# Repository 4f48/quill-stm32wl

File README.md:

# Quill STM32 WL

An Adafruit Feather-sized STM32 development board with integrated 868 MHz LoRa radio.

## Features
- 32-bit ARM Cortex-M4 48 MHz microcontroller
- 256 kb flash, 64 kb RAM
- LoRa P2P/LoRaWAN - Up to 15 km range with a good antenna
- Programmable via SWD/UART/USB or control with AT Commands
- Built-in 3.3V linear regulator, providing up to 600 mA
- JST PH battery connector, built-in charging
- USB-C port for power supply, USB serial, battery charging
- Adafruit Feather-compatible dimensions
- STEMMA QT/Qwiic connector for soldering-free I2C

## Why though
I made Quill STM32 WL because I was unsatisfied with existing LoRa/long-range wireless development boards. They are either low-effort modules with ESP32 chips and huge power consumption, or use outdated parts and standards. I really liked the Adafruit Feather RP2040 RFM95 due to its size, feature-set, but it uses the older Semtech SX1276 LoRa IC.

As I was scrolling through ST Microelectronic's website (as one does), I found the perfect match: the STM32WLE5 family of microcontrollers. They offer an improved LoRa solution - with up to +22 dBm output power - in a sleek package, with an integrated, low-power STM32 microcontroller. I knew I had to try making something with it.

This was my second PCB project ever, and digging into more complicated concepts and trying to make a more dense board layout was a great challenge and an opportunity to improve my skills, before starting even more complicated projects.

## Usage
You can either use Quill STM32 WL as a standalone microcontroller, by programming it via the 3-pin SWD port or USB serial, or by sending AT Commands to the UART2 serial bus on pins 12 (RX) and 13 (TX) if you just wish to use the LoRa/LoRaWAN capabilities.

For programming instructions, see [RAK3172 Low Level Development Reference](https://docs.rakwireless.com/product-categories/wisduo/rak3172-module/low-level-development/). For using the AT Command interface, see [RAK3172 AT Command Manual](https://docs.rakwireless.com/product-categories/wisduo/rak3172-module/at-command-manual/).

This board is really versatile and could be used for a wide variety of projects. Note that the MCU is not as fast as some other offerings on the market, thus it can't be used for advanced data processing. However, Quill STM32 WL is more than capable of driving sensors (for example outdoor air monitoring) and some basic processing tasks, and thanks to its LoRa capabilities, it can radio data through long distances, ideally several kilometers with clear line-of-sight, which is particularly useful for off-grid IOT systems, as an example.

## Build one yourself!
In theory, you could make one of these boards for yourself. Uploading the provided Gerber files to a PCB manufacturing service (JLCPCB, PCBWay, Aisler, etc.) is simple, not very expensive and you usually get the boards quickly. You can find the production files in [/production](https://github.com/4f48/quill-stm32wl/tree/main/production).

However, placing and soldering the SMD components on the board may prove difficult, especially if you never soldered anything before. The design uses 0402 (1005 metric) passive components to fit into the space-confined size of the board. While it may not seem like on the screen, these components are REALLY tiny. You might find it easier to have the manufacturing service mount the components for you, but that gets very expensive very fast. For example, making 5 fully assembled Quill STM32 WL with JLCPCB would cost around $130 plus shipping. Reflow/hot-air soldering is an option, but you need to have specific equipment for that.

If you still want to make one of these yourself, feel free to explore these files in this repository, they will help greatly:

- Schematic: [schematic.svg](https://github.com/4f48/quill-stm32wl/blob/main/assets/schematic.svg)
- KiCad PCB: [quill-stm32wl.kicad_pcb](https://github.com/4f48/quill-stm32wl/blob/main/quill-stm32wl.kicad_pcb)
- Bill of Materials: [bom.csv](https://github.com/4f48/quill-stm32wl/blob/main/bom.csv)/[bom.ods](https://github.com/4f48/quill-stm32wl/blob/main/bom.ods)
- 3D model: [quill_stm32wl.step](https://github.com/4f48/quill-stm32wl/blob/main/assets/quill_stm32wl.step)

## Fallout Zine
Check out the magazine page for this project. Or [download PDF](https://raw.githubusercontent.com/4f48/quill-stm32wl/refs/heads/main/assets/magazine_page.pdf).

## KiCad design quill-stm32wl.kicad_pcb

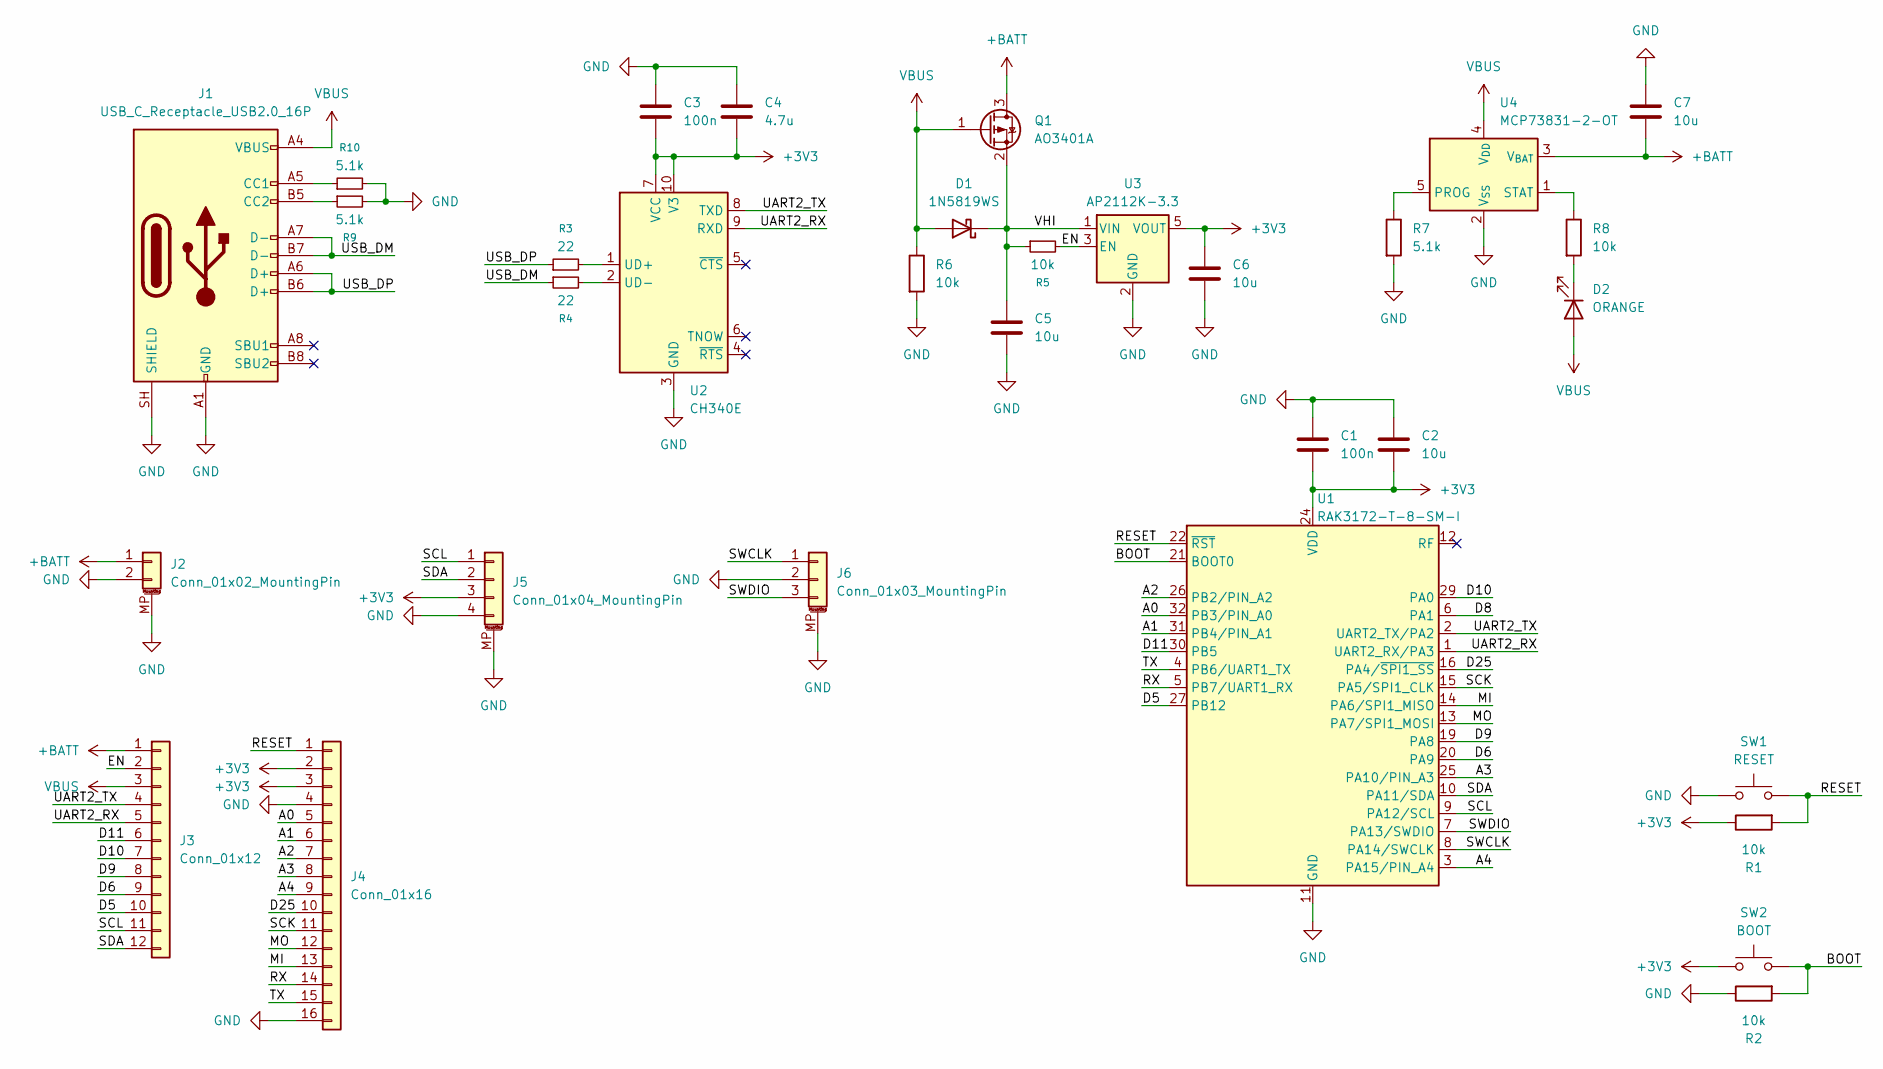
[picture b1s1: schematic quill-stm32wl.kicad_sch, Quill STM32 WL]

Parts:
C1, C3: 100n; C_0402_1005Metric
C2, C5, C6, C7: 10u; C_0603_1608Metric
C4: 4.7u; C_0402_1005Metric
D1: 1N5819WS; D_SOD-323
D2: ORANGE; LED_0402_1005Metric
J1: USB_C_Receptacle_USB2.0_16P; USB_C_Receptacle_GCT_USB4105-xx-A_16P_TopMnt_Horizontal
J2: Conn_01x02_MountingPin; JST_PH_S2B-PH-SM4-TB_1x02-1MP_P2.00mm_Horizontal
J3: Conn_01x12; PinHeader_1x12_P2.54mm_Vertical
J4: Conn_01x16; PinHeader_1x16_P2.54mm_Vertical
J5: Conn_01x04_MountingPin; JST_SH_BM04B-SRSS-TB_1x04-1MP_P1.00mm_Vertical
J6: Conn_01x03_MountingPin; JST_SH_BM03B-SRSS-TB_1x03-1MP_P1.00mm_Vertical
Q1: AO3401A; SOT-23
R1, R2, R5, R6, R8: 10k; R_0402_1005Metric
R3, R4: 22; R_0402_1005Metric
R7, R9, R10: 5.1k; R_0402_1005Metric
SW1: RESET; SW_SPST_PTS810
SW2: BOOT; SW_SPST_PTS810
U1: RAK3172-T-8-SM-I; RAK3172
U2: CH340E; MSOP-10_3x3mm_P0.5mm
U3: AP2112K-3.3; SOT-23-5
U4: MCP73831-2-OT; SOT-23-5

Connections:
+3V3: C1.2, C2.2, C3.2, C4.2, C6.1, J4.2, J4.3, J5.3, R1.1, SW2.1, U1.24 (VDD), U2.7 (VCC), U2.10 (V3), U3.5 (VOUT)
+BATT: C7.2, J2.1, J3.1, Q1.3 (D), U4.3 (V_{BAT})
/A0: J4.5, U1.32 (PB3/PIN_A0)
/A1: J4.6, U1.31 (PB4/PIN_A1)
/A2: J4.7, U1.26 (PB2/PIN_A2)
/A3: J4.8, U1.25 (PA10/PIN_A3)
/A4: J4.9, U1.3 (PA15/PIN_A4)
/BOOT: R2.2, SW2.2, U1.21 (BOOT0)
/D5: J3.10, U1.27 (PB12)
/D6: J3.9, U1.20 (PA9)
/D8: U1.6 (PA1)
/D9: J3.8, U1.19 (PA8)
/D10: J3.7, U1.29 (PA0)
/D11: J3.6, U1.30 (PB5)
/D25: J4.10, U1.16 (PA4/~SPI1_SS)
/EN: J3.2, R5.2, U3.3 (EN)
/MI: J4.13, U1.14 (PA6/SPI1_MISO)
/MO: J4.12, U1.13 (PA7/SPI1_MOSI)
/RESET: J4.1, R1.2, SW1.2, U1.22 (~RST)
/RX: J4.14, U1.5 (PB7/UART1_RX)
/SCK: J4.11, U1.15 (PA5/SPI1_CLK)
/SCL: J3.11, J5.1, U1.9 (PA12/SCL)
/SDA: J3.12, J5.2, U1.10 (PA11/SDA)
/SWCLK: J6.1, U1.8 (PA14/SWCLK)
/SWDIO: J6.3, U1.7 (PA13/SWDIO)
/TX: J4.15, U1.4 (PB6/UART1_TX)
/UART2_RX: J3.5, U1.1 (UART2_RX/PA3), U2.9 (RXD)
/UART2_TX: J3.4, U1.2 (UART2_TX/PA2), U2.8 (TXD)
/USB_DM: J1.A7 (D-), J1.B7 (D-), R4.1
/USB_DP: J1.A6 (D+), J1.B6 (D+), R3.1
/VHI: C5.1, D1.1 (K), Q1.2 (S), R5.1, U3.1 (VIN)
GND: C1.1, C2.1, C3.1, C4.1, C5.2, C6.2, C7.1, J1.A1 (GND), J1.A12 (GND), J1.B1 (GND), J1.B12 (GND), J1.SH (SHIELD), J2.2, J2.MP (MountPin), J4.4, J4.16, J5.4, J5.MP (MountPin), J6.2, J6.MP (MountPin), R2.1, R6.2, R7.2, R9.2, R10.2, SW1.1, U1.11 (GND), U1.17 (GND), U1.18 (GND), U1.23 (GND), U1.28 (GND), U2.3 (GND), U3.2 (GND), U4.2 (V_{SS})
unnamed: D2.1 (K), R8.2
unnamed: J1.A5 (CC1), R10.1
unnamed: J1.B5 (CC2), R9.1
unnamed: R3.2, U2.1 (UD+)
unnamed: R4.2, U2.2 (UD-)
unnamed: R7.1, U4.5 (PROG)
unnamed: R8.1, U4.1 (STAT)
VBUS: D1.2 (A), D2.2 (A), J1.A4 (VBUS), J1.A9 (VBUS), J1.B4 (VBUS), J1.B9 (VBUS), J3.3, Q1.1 (G), R6.1, U4.4 (V_{DD})

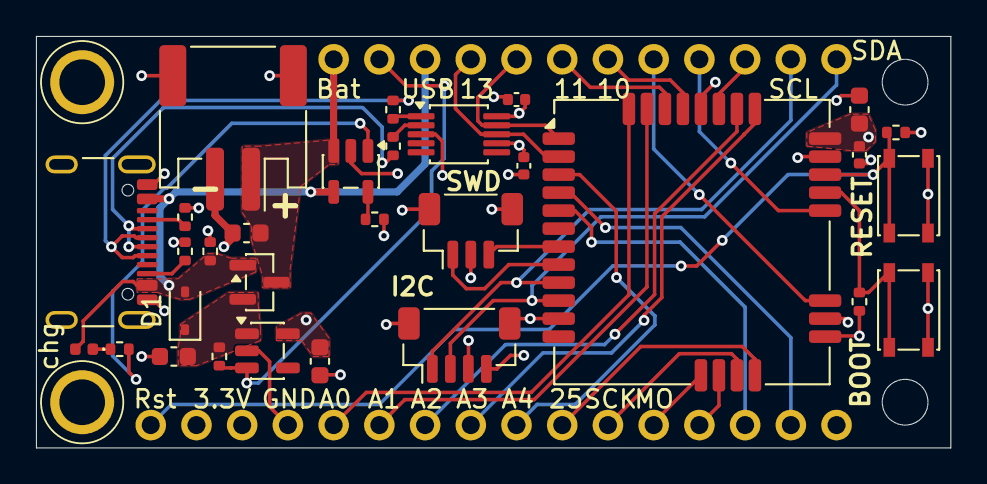
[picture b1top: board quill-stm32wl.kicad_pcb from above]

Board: 4 copper layers, 50.8 x 22.9 mm, 32 parts (0 on the bottom side), 39 nets.

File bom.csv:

Designator,Footprint,Quantity,Value,MPN,Link
"C1, C3",0402,2,100n,GXT155R71E104KE01D,https://mou.sr/3ReCbrt
"C2, C5, C6, C7",0603,4,10u,GRM188Z71A106KA73D,https://mou.sr/3QT9dgV
C4,0402,1,4.7u,GRM155C80J475MEAAJ,https://mou.sr/4tpjte7
D1,D_SOD-323,1,1N5819WS,1N5819WS,https://www.digikey.com/en/products/detail/shenzhen-slkormic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
D2,0402,1,ORANGE,APHHS1005SECK,https://mou.sr/4tAjQTp
J1,USB_C_Receptacle_GCT_USB4105-xx-A_16P_TopMnt_Horizontal,1,USB_C_Receptacle_USB2.0_16P,USB4105-GF-A,https://mou.sr/3F3o9Qf
J2,JST_PH_S2B-PH-SM4-TB_1x02-1MP_P2.00mm_Horizontal,1,Conn_01x02_MountingPin,S2B-PH-SM4-TB(LF)(SN),https://mou.sr/4uEPik3
J5,JST_SH_BM04B-SRSS-TB_1x04-1MP_P1.00mm_Vertical,1,Conn_01x04_MountingPin,BM04B-SRSS-TB(LF)(SN),https://mou.sr/4nlOzC0
J6,JST_SH_BM03B-SRSS-TB_1x03-1MP_P1.00mm_Vertical,1,Conn_01x03_MountingPin,BM03B-SRSS-TB(LF)(SN),https://mou.sr/3PbSNQ8
Q1,SOT-23,1,AO3401A,AO3401A,https://www.digikey.hu/short/twfrrn3w
"R1, R2, R5, R6, R8",0402,5,10k,RC0402JR-7D10KL,https://mou.sr/3Qyq83Z
"R10, R7, R9",0402,3,5.1k,RC0402JR-075K1P,https://mou.sr/4djlcvs
"R3, R4",0402,2,22,RC0402JR-0722RL,https://mou.sr/3WMWZH5
SW1,SW_SPST_PTS810,1,RESET,PTS810SJM250SMTR LFS,https://mou.sr/4v3Dg4j
SW2,SW_SPST_PTS810,1,BOOT,PTS810SJM250SMTR LFS,https://mou.sr/4v3Dg4j
U1,RAK3172,1,RAK3172-T-8-SM-I,RAK3172-T-8-SM-I,https://www.lcsc.com/product-detail/C19723908.html?s_z=n_q_r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
U2,MSOP-10_3x3mm_P0.5mm,1,CH340E,CH340E,https://www.lcsc.com/product-detail/C99652.html?s_z=n_q_CH34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
U3,SOT-23-5,1,AP2112K-3.3,AP2112K-3.3TRG1,https://mou.sr/41TpKUl
U4,SOT-23-5,1,MCP73831-2-OT,MCP73831T-2ACI/OT,https://mou.sr/3ThCNeY

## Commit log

2026-05-11 upload project
2026-05-11 start documentation
2026-05-12 assets, links, complete bom
2026-05-12 add note about prod files
2026-05-13 add magazine page
2026-05-13 add magazine page to readme
2026-05-13 add link to pdf

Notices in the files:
quill-stm32wl.kicad_pcb:
© Olivér Pirger
quill-stm32wl.kicad_sch:
Copyright (C) 2026 Olivér Pirger
